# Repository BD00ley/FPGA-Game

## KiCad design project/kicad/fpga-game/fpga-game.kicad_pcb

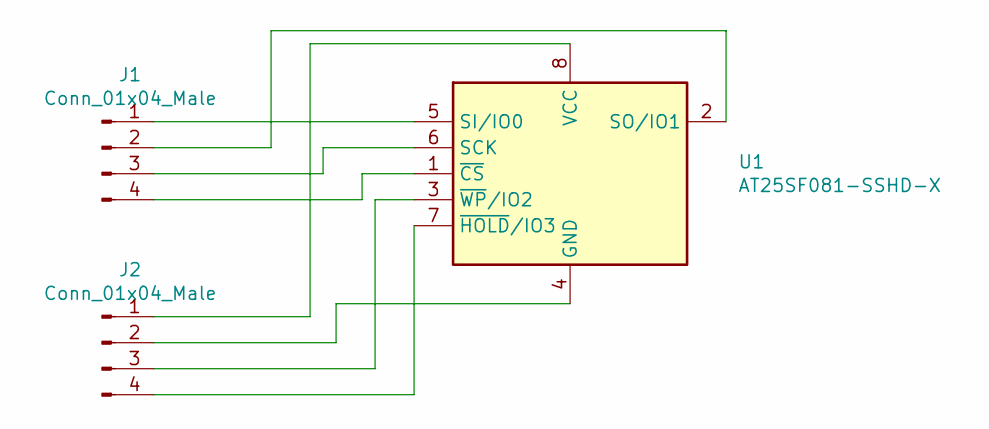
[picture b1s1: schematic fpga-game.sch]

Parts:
J1, J2: Conn_01x04_Male; PinHeader_1x04_P1.00mm_Vertical
U1: AT25SF081-SSHD-X; SOIC-8_3.9x4.9mm_P1.27mm

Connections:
unnamed: J1.1, U1.5 (SI/IO0)
unnamed: J1.2, U1.2 (SO/IO1)
unnamed: J1.3, U1.6 (SCK)
unnamed: J1.4, U1.1 (~CS)
unnamed: J2.1, U1.8 (VCC)
unnamed: J2.2, U1.4 (GND)
unnamed: J2.3, U1.3 (~WP~/IO2)
unnamed: J2.4, U1.7 (~HOLD~/IO3)

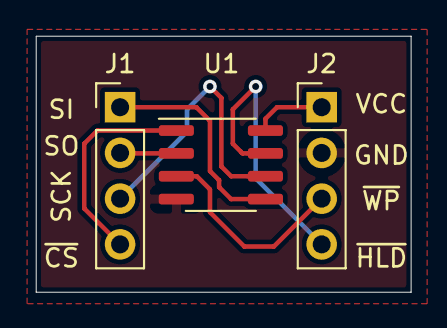
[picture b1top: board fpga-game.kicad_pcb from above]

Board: 2 copper layers, 20.8 x 14.2 mm, 3 parts (0 on the bottom side), 8 nets.

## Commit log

2020-10-17 source commit
2020-10-24 vga timing module done
2020-10-31 more things in .gitignore; added binary image creation script + test picture; added kicad project for memory breakout board; added initial files for fifo, memory controller and top level
2020-11-20 MOSI of SPI module appears to be working
2020-11-23 removed pcb for flash memory (using a premade soic-8 to dip instead); MISO of the SPI appears to be working (will clean up later lmao)
2020-11-23 accidently only commited tb; see previous commit for details
2020-12-15 moved source to SystemVerilog (Verilog code still works and SV is just better). Added a makefile and MOSI is tested working on the board
2021-01-05 SPI MOSI mode 0 consistenly working on hardware
